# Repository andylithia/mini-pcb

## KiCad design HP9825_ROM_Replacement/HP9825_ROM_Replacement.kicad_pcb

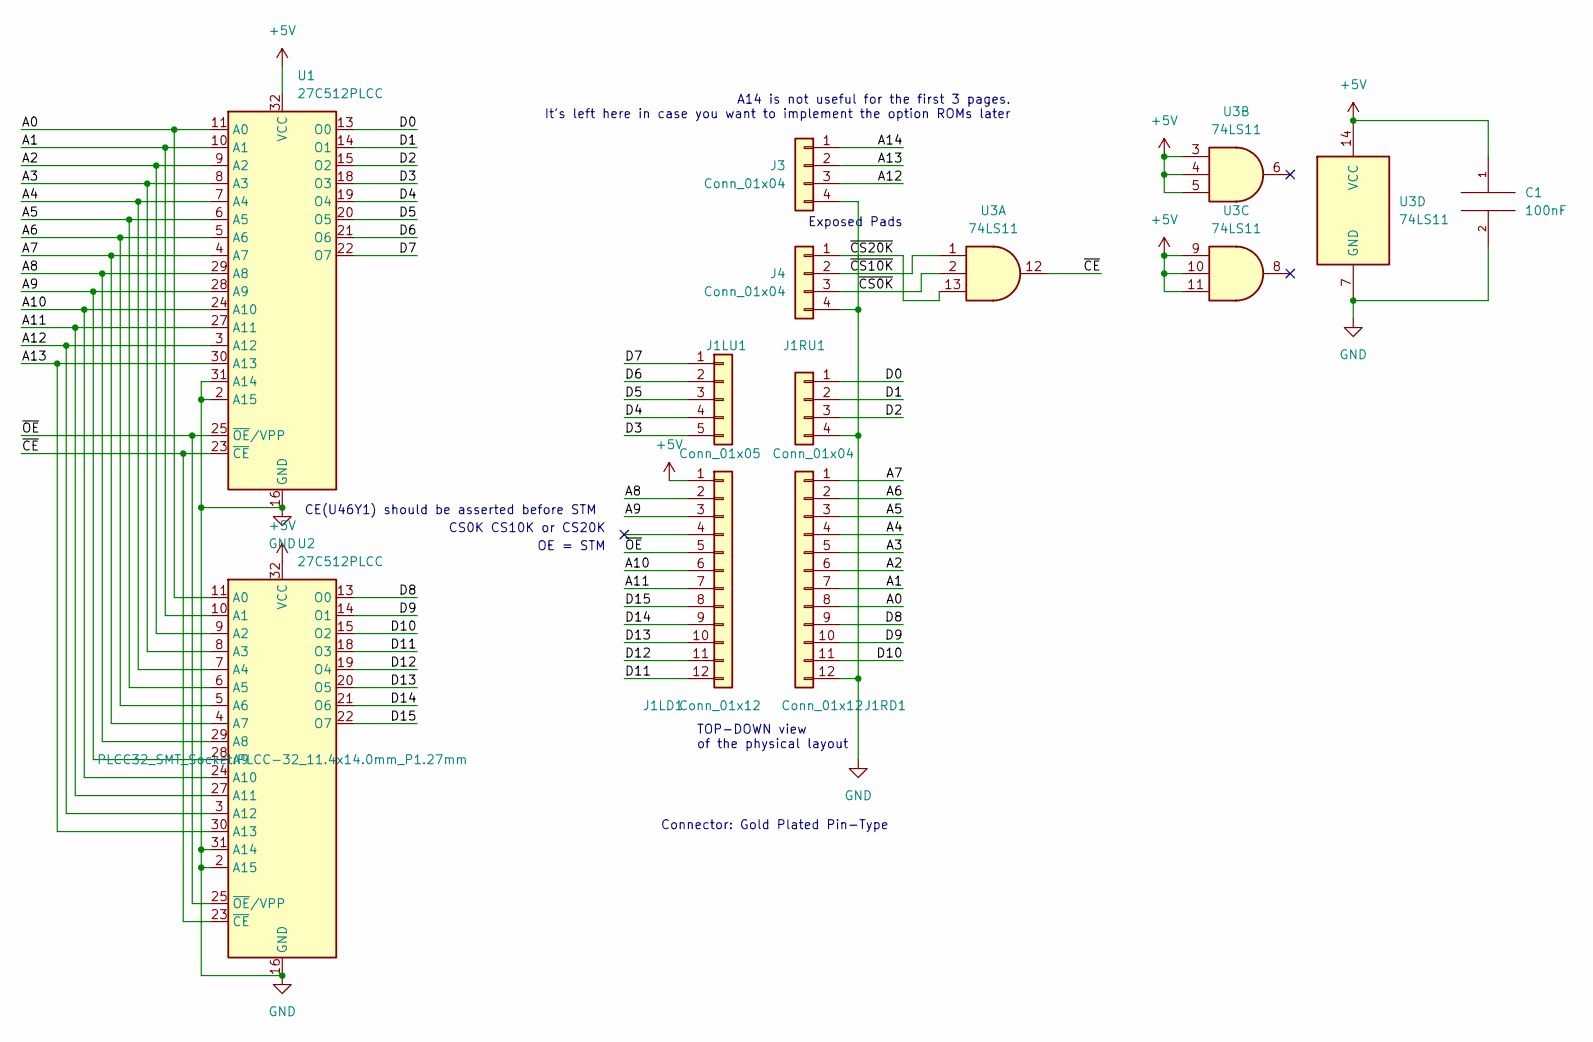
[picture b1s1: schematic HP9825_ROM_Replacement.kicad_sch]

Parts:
C1: 100nF; C_0603_1608Metric
J1LD1, J1RD1: Conn_01x12; PinHeader_1x12_P2.54mm_Vertical
J1LU1: Conn_01x05; PinHeader_1x05_P2.54mm_Vertical
J1RU1, J3, J4: Conn_01x04; PinHeader_1x04_P2.54mm_Vertical
U1, U2: 27C512PLCC; PLCC-32_11.4x14.0mm_P1.27mm
U3: 74LS11; DIP-14_W8.89mm_SMDSocket_LongPads

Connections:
+5V: C1.1, J1LD1.1, U1.32 (VCC), U2.32 (VCC), U3.3, U3.4, U3.5, U3.9, U3.10, U3.11, U3.14 (VCC)
/A0: J1RD1.8, U1.11 (A0), U2.11 (A0)
/A1: J1RD1.7, U1.10 (A1), U2.10 (A1)
/A2: J1RD1.6, U1.9 (A2), U2.9 (A2)
/A3: J1RD1.5, U1.8 (A3), U2.8 (A3)
/A4: J1RD1.4, U1.7 (A4), U2.7 (A4)
/A5: J1RD1.3, U1.6 (A5), U2.6 (A5)
/A6: J1RD1.2, U1.5 (A6), U2.5 (A6)
/A7: J1RD1.1, U1.4 (A7), U2.4 (A7)
/A8: J1LD1.2, U1.29 (A8), U2.29 (A8)
/A9: J1LD1.3, U1.28 (A9), U2.28 (A9)
/A10: J1LD1.6, U1.24 (A10), U2.24 (A10)
/A11: J1LD1.7, U1.27 (A11), U2.27 (A11)
/A12: J3.3, U1.3 (A12), U2.3 (A12)
/A13: J3.2, U1.30 (A13), U2.30 (A13)
/A14: J3.1
/D0: J1RU1.1, U1.13 (O0)
/D1: J1RU1.2, U1.14 (O1)
/D2: J1RU1.3, U1.15 (O2)
/D3: J1LU1.5, U1.18 (O3)
/D4: J1LU1.4, U1.19 (O4)
/D5: J1LU1.3, U1.20 (O5)
/D6: J1LU1.2, U1.21 (O6)
/D7: J1LU1.1, U1.22 (O7)
/D8: J1RD1.9, U2.13 (O0)
/D9: J1RD1.10, U2.14 (O1)
/D10: J1RD1.11, U2.15 (O2)
/D11: J1LD1.12, U2.18 (O3)
/D12: J1LD1.11, U2.19 (O4)
/D13: J1LD1.10, U2.20 (O5)
/D14: J1LD1.9, U2.21 (O6)
/D15: J1LD1.8, U2.22 (O7)
/~CE: U1.23 (~CE), U2.23 (~CE), U3.12
/~CS0K: J4.3, U3.2
/~CS10K: J4.2, U3.1
/~CS20K: J4.1, U3.13
/~OE: J1LD1.5, U1.25 (~OE/VPP), U2.25 (~OE/VPP)
GND: C1.2, J1RD1.12, J1RU1.4, J3.4, J4.4, U1.2 (A15), U1.16 (GND), U1.31 (A14), U2.2 (A15), U2.16 (GND), U2.31 (A14), U3.7 (GND)

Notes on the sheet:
TOP-DOWN view of the physical layout
OE = STM
CE(U46Y1) should be asserted before STM
Exposed Pads
Connector: Gold Plated Pin-Type
CS0K CS10K or CS20K
A14 is not useful for the first 3 pages. It's left here in case you want to implement the option ROMs later

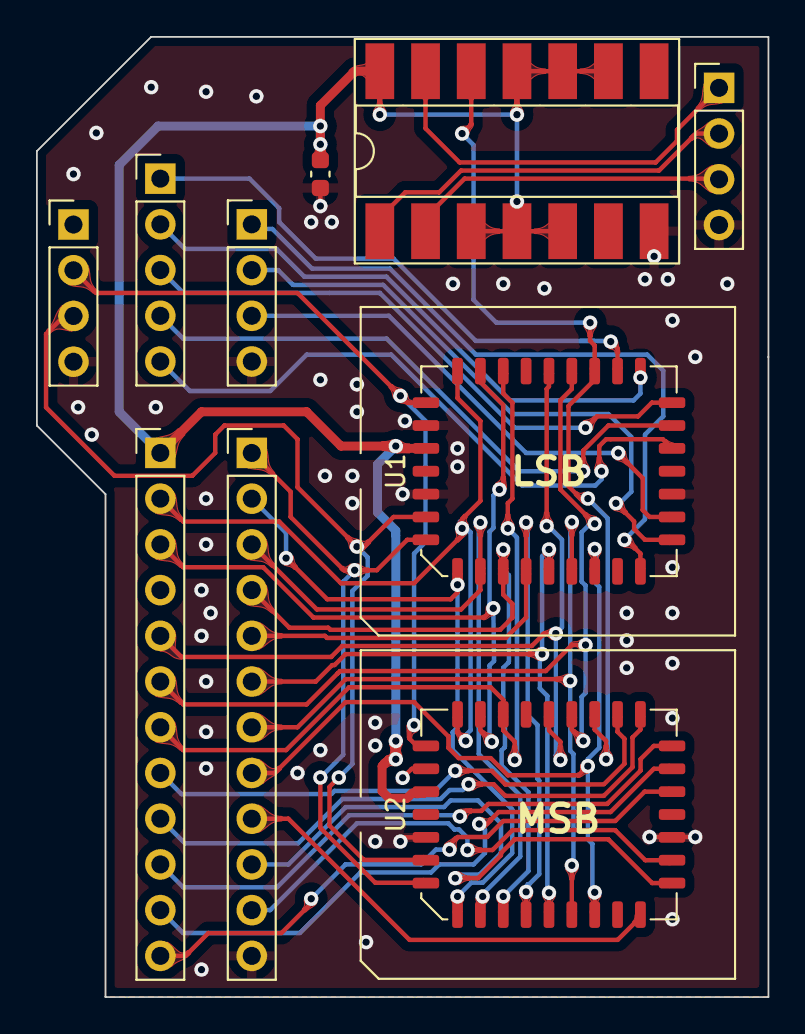
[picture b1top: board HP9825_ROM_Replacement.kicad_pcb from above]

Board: 2 copper layers, 40.6 x 53.3 mm, 10 parts (0 on the bottom side), 37 nets.

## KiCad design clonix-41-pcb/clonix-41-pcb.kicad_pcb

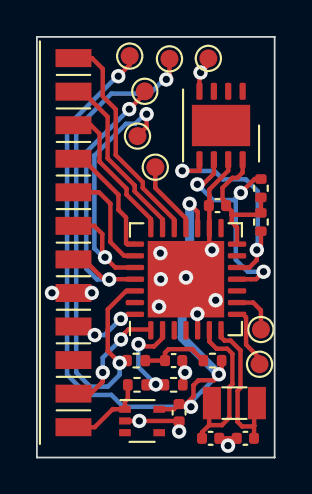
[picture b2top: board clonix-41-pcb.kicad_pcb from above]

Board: 2 copper layers, 13.2 x 23.4 mm, 24 parts (0 on the bottom side), 23 nets.

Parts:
C1, C4, C5: 100n; C_0402_1005Metric
C2, C3: 10p; C_0402_1005Metric
J1: HP41MOD-CONN; HP41MOD
R1, R2, R5: 10K; R_0402_1005Metric
R3, R4: 100K; R_0402_1005Metric
R6: 470; R_0402_1005Metric
TP1, TP2, TP3, TP4, TP5, TP6, TP7, TP9: TestPoint; TestPoint_Pad_D1.0mm
U1: TLV70033_SOT353; SOT-353_SC-70-5
U2: PIC18F26K83-IML; QFN-28-1EP_6x6mm_P0.65mm_EP4.25x4.25mm
U3: FM24C64B; DFN-8-1EP_4x4mm_P0.8mm_EP2.3x3.24mm
Y1: Crystal; Crystal_SMD_3215-2Pin_3.2x1.5mm

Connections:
+3V3: C1.1, R5.1, TP1.1, U1.5 (OUT), U2.17 (VDD)
/MCLRn: R6.2, TP2.1, U2.26 (VPP/~MCLR/RE3)
/NUTB3: J1.11 (B3), U2.28 (RA1)
/NUTB4: J1.12 (B4), U2.1 (RA2)
/NUTDATA: J1.4 (DATA), TP4.1, U2.24 (ICSPCLK/RB6)
/NUTFI: J1.9 (FI), U2.23 (RB5)
/NUTISA: J1.5 (ISA), U2.22 (RB4)
/NUTPHI1: J1.7 (ph1), U2.19 (RB1)
/NUTPHI2: J1.6 (phi2), U2.20 (RB2)
/NUTPWO: J1.10 (PWO), TP3.1, U2.25 (ICSPDAT/RB7)
/NUTSYNC: J1.8 (SYNC), U2.21 (RB3)
/RAMCLK: R1.2, U2.11 (RC3), U3.6 (SCL)
/RAMDAT: R2.2, U2.12 (RC4), U3.5 (SDA)
/RAMPOW: C4.1, R1.1, R2.1, U2.14 (RC6), U3.8 (VDD)
/VBAT: J1.1 (VBAT), R3.1, U1.1 (IN)
/VBAT_SENSE: R3.2, R4.1, U2.2 (RA3)
GND: C1.2, C2.2, C3.2, C4.2, C5.2, J1.3 (GND), R4.2, TP5.1, U1.2 (GND), U2.5 (VSS), U2.16 (VSS), U2.29 (VSS), U3.4 (VSS), U3.7 (WP)
unnamed: C2.1, U2.7 (OSC1_CLKIN/RA7), Y1.1
unnamed: C3.1, U2.6 (OSC2_CLKOUT/RA6), Y1.2
unnamed: C5.1, R5.2, R6.1
unnamed: TP6.1, U2.8 (RC0/SOSCO)
unnamed: TP7.1, U2.9 (RC1/SOSCI)
unnamed: TP9.1, U2.18 (RB0)

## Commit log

2022-05-17 NoVRAM Clone Version 0
2022-07-04 HP 9825 ROM Replacement Touch-up
